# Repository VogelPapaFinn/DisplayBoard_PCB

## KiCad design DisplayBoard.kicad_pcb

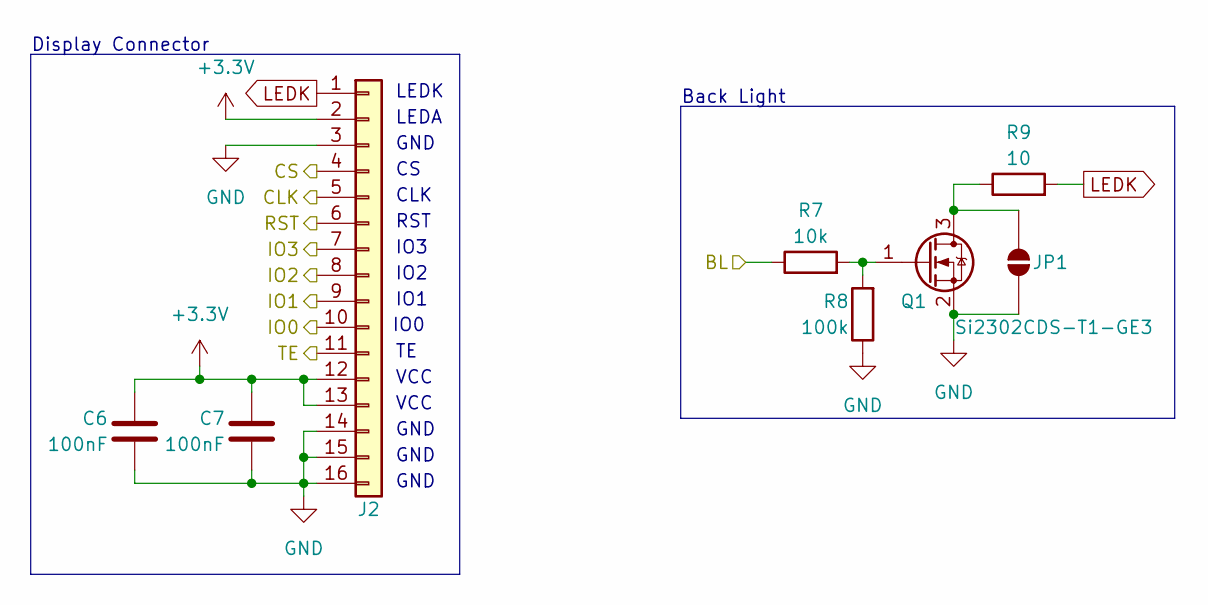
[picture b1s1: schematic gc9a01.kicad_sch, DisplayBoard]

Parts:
C6, C7: 100nF; C_0805_2012Metric
J2: Conn_01x16; ST77916
JP1: SolderJumper_2_Open; SolderJumper-2_P1.3mm_Open_Pad1.0x1.5mm
Q1: Si2302CDS-T1-GE3; SOT-23
R7: 10k; R_0603_1608Metric
R8: 100k; R_0603_1608Metric
R9: 10; R_0603_1608Metric

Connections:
+3.3V: C6.1, C7.1, J2.2, J2.12, J2.13; also elsewhere on the board
/Display/BL: R7.1; also elsewhere on the board
/Display/CLK: J2.5; also elsewhere on the board
/Display/CS: J2.4; also elsewhere on the board
/Display/IO0: J2.10; also elsewhere on the board
/Display/IO1: J2.9; also elsewhere on the board
/Display/IO2: J2.8; also elsewhere on the board
/Display/IO3: J2.7; also elsewhere on the board
/Display/RST: J2.6; also elsewhere on the board
/Display/TE: J2.11; also elsewhere on the board
GND: C6.2, C7.2, J2.3, J2.14, J2.15, J2.16, JP1.2 (B), Q1.2 (S), R8.1; also elsewhere on the board
LEDK: J2.1, R9.2
unnamed: JP1.1 (A), Q1.3 (D), R9.1
unnamed: Q1.1 (G), R7.2, R8.2

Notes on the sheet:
IO1
IO0
GND
VCC
LEDA
Display Connector
Back Light
IO2
CLK
LEDK
RST
IO3

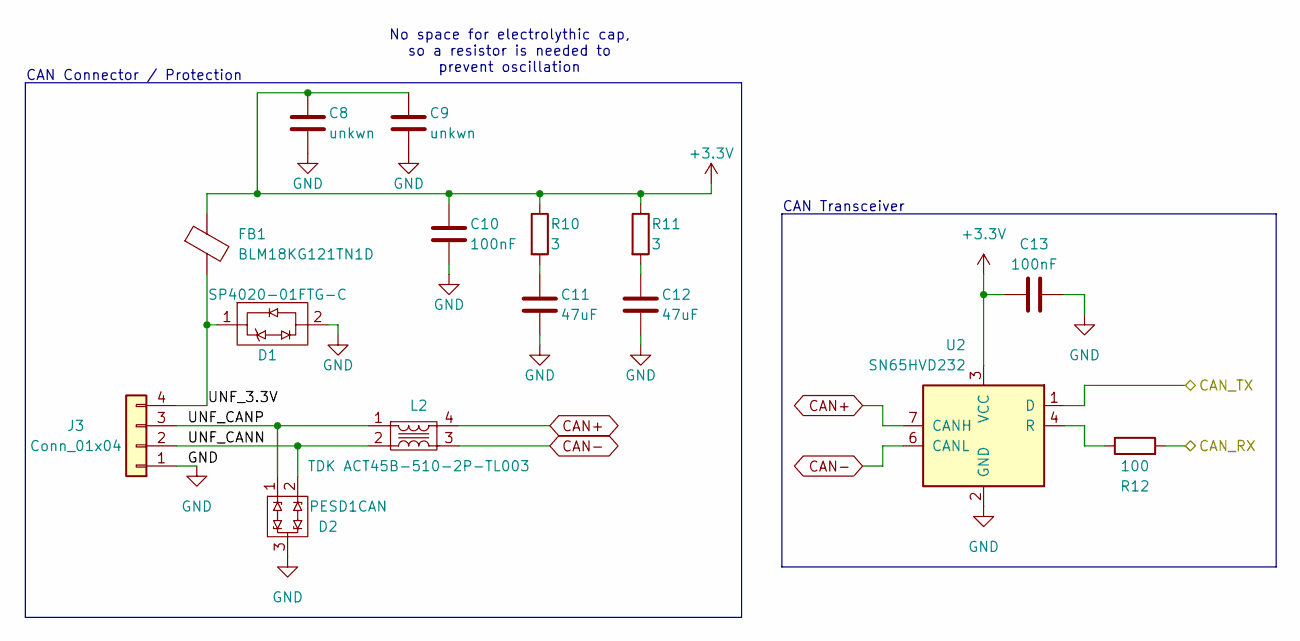
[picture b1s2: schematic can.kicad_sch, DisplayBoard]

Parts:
C8, C9: unkwn; C_0805_2012Metric
C10, C13: 100nF; C_0805_2012Metric
C11, C12: 47uF; C_0805_2012Metric
D1: SP4020-01FTG-C; D_SOD-323
D2: PESD1CAN; SOT-23
FB1: BLM18KG121TN1D; L_0603_1608Metric
J3: Conn_01x04; JST_PH_B4B-PH-SM4-TB_1x04-1MP_P2.00mm_Vertical
L2: TDK ACT45B-510-2P-TL003
R10, R11: 3; R_0603_1608Metric
R12: 100; R_0603_1608Metric
U2: SN65HVD232; SOIC-8_3.9x4.9mm_P1.27mm

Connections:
+3.3V: C8.1, C9.1, C10.1, C13.1, FB1.1, R10.1, R11.1, U2.3 (VCC); also elsewhere on the board
/CAN/CAN_RX: R12.2; also elsewhere on the board
/CAN/CAN_TX: U2.1 (D); also elsewhere on the board
/CAN/UNF_3.3V: D1.1, FB1.2, J3.4
/CAN/UNF_CANN: D2.2, J3.2, L2.2
/CAN/UNF_CANP: D2.1, J3.3, L2.1
CAN+: L2.4, U2.7 (CANH)
CAN-: L2.3, U2.6 (CANL)
GND: C8.2, C9.2, C10.2, C11.2, C12.2, C13.2, D1.2, D2.3, J3.1, U2.2 (GND); also elsewhere on the board
unnamed: C11.1, R10.2
unnamed: C12.1, R11.2
unnamed: R12.1, U2.4 (R)

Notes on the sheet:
No space for electrolythic cap, so a resistor is needed to prevent oscillation
CAN Transceiver
CAN Connector / Protection

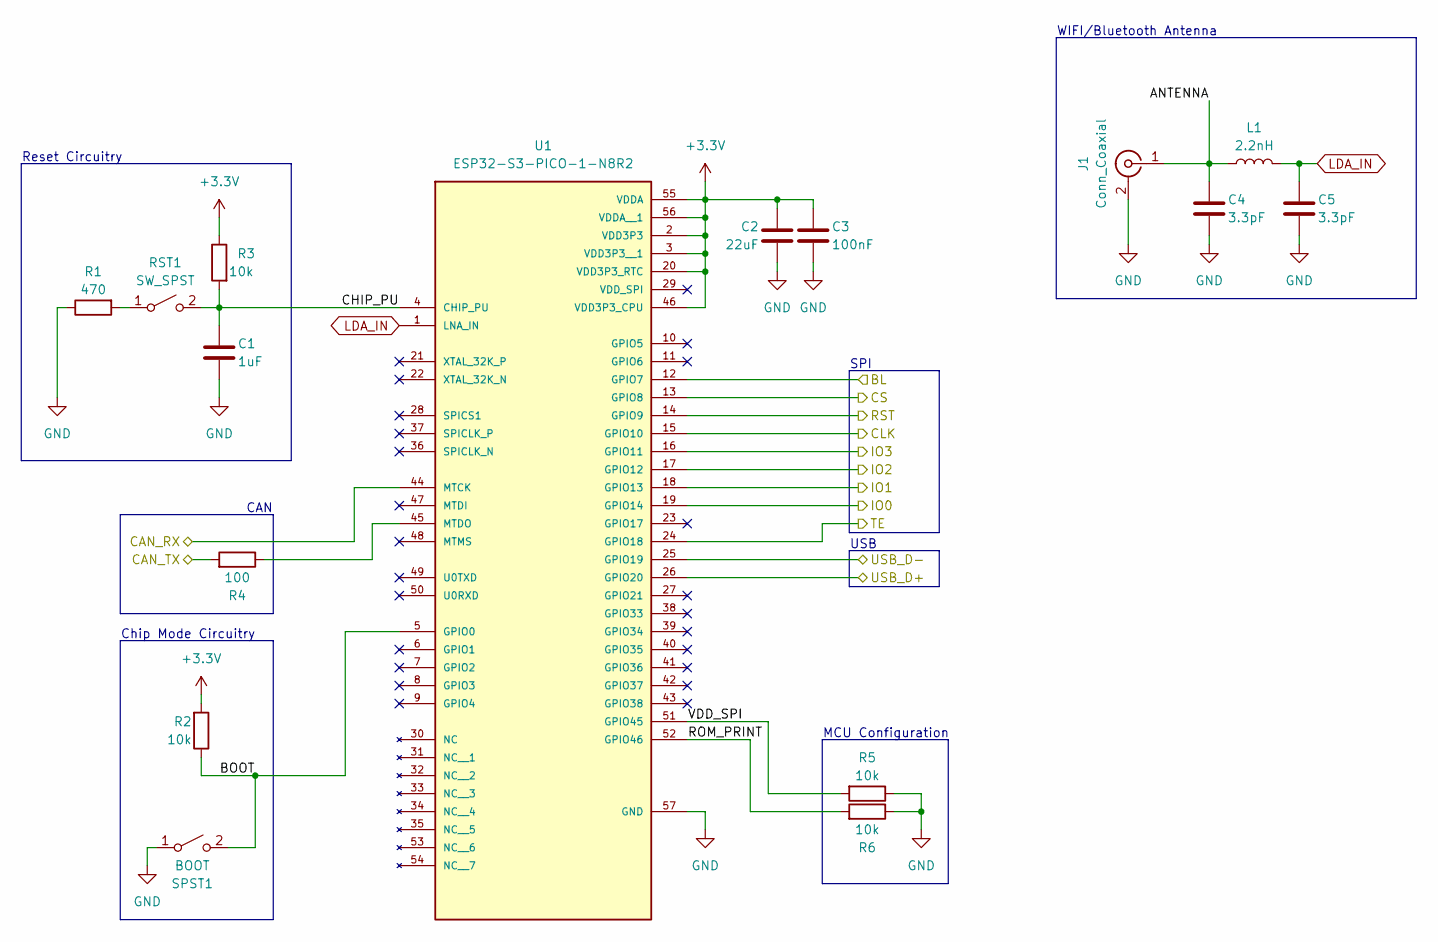
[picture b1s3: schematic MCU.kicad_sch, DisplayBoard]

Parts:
C1: 1uF; C_0805_2012Metric
C2: 22uF; C_0805_2012Metric
C3: 100nF; C_0805_2012Metric
C4, C5: 3.3pF; C_0603_1608Metric
J1: Conn_Coaxial; CONMHF1-SMD-G-T_U.FL
L1: 2.2nH; L_0603_1608Metric
R1: 470; R_0603_1608Metric
R2, R3, R5, R6: 10k; R_0603_1608Metric
R4: 100; R_0603_1608Metric
RST1: SW_SPST; XUNPU_Button
SPST1: BOOT; XUNPU_Button
U1: ESP32-S3-PICO-1-N8R2; ESP32-S3-PICO-1; PARTREV 1.0

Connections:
+3.3V: C2.1, C3.1, R2.2, R3.1, U1.2 (VDD3P3), U1.3 (VDD3P3__1), U1.20 (VDD3P3_RTC), U1.46 (VDD3P3_CPU), U1.55 (VDDA), U1.56 (VDDA__1); also elsewhere on the board
/CAN/CAN_RX: U1.44 (MTCK); also elsewhere on the board
/CAN/CAN_TX: R4.2; also elsewhere on the board
/Display/BL: U1.12 (GPIO7); also elsewhere on the board
/Display/CLK: U1.15 (GPIO10); also elsewhere on the board
/Display/CS: U1.13 (GPIO8); also elsewhere on the board
/Display/IO0: U1.19 (GPIO14); also elsewhere on the board
/Display/IO1: U1.18 (GPIO13); also elsewhere on the board
/Display/IO2: U1.17 (GPIO12); also elsewhere on the board
/Display/IO3: U1.16 (GPIO11); also elsewhere on the board
/Display/RST: U1.14 (GPIO9); also elsewhere on the board
/Display/TE: U1.24 (GPIO18); also elsewhere on the board
/MCU/ANTENNA: C4.1, J1.1 (In), L1.1
/MCU/BOOT: R2.1, SPST1.2 (B), U1.5 (GPIO0)
/MCU/CHIP_PU: C1.1, R3.2, RST1.2 (B), U1.4 (CHIP_PU)
/MCU/ROM_PRINT: R6.2, U1.52 (GPIO46)
/MCU/USB_D+: U1.26 (GPIO20); also elsewhere on the board
/MCU/USB_D-: U1.25 (GPIO19); also elsewhere on the board
/MCU/VDD_SPI: R5.2, U1.51 (GPIO45)
GND: C1.2, C2.2, C3.2, C4.2, C5.2, J1.2 (Ext), R1.1, R5.1, R6.1, SPST1.1 (A), U1.57 (GND); also elsewhere on the board
LDA_IN: C5.1, L1.2, U1.1 (LNA_IN)
unnamed: R1.2, RST1.1 (A)
unnamed: R4.1, U1.45 (MTDO)

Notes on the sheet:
Chip Mode Circuitry
USB
Reset Circuitry
WIFI/Bluetooth Antenna
MCU Configuration
SPI
CAN

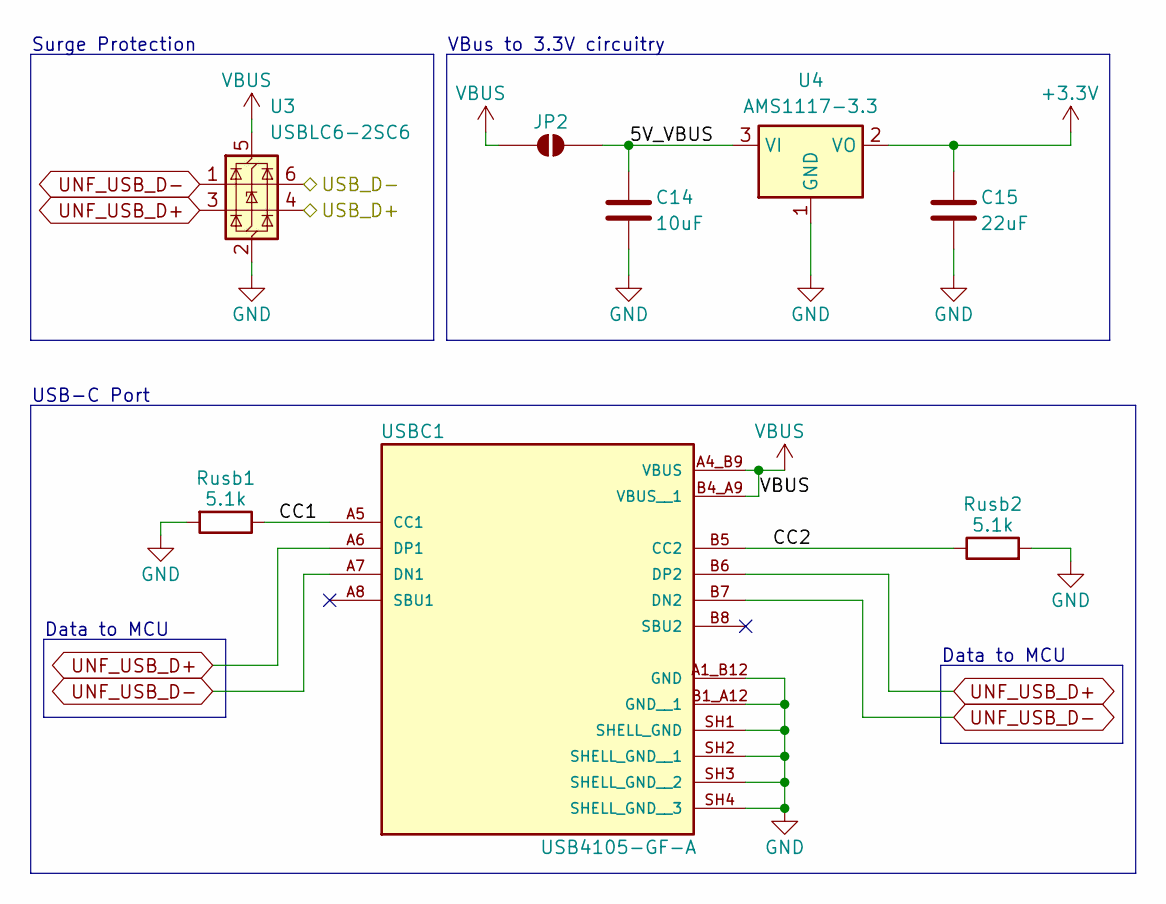
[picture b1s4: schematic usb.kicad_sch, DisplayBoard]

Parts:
C14: 10uF; C_0805_2012Metric
C15: 22uF; C_0805_2012Metric
JP2: SolderJumper_2_Open; SolderJumper-2_P1.3mm_Open_RoundedPad1.0x1.5mm
Rusb1, Rusb2: 5.1k; R_0603_1608Metric
U3: USBLC6-2SC6; SOT-23-6
U4: AMS1117-3.3; SOT-223-3_TabPin2
USBC1: USB4105-GF-A; USB-C_24P-2.0; PARTREV B4

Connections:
+3.3V: C15.1, U4.2 (VO); also elsewhere on the board
/MCU/USB_D+: U3.4 (I/O2); also elsewhere on the board
/MCU/USB_D-: U3.6 (I/O1); also elsewhere on the board
/USB/5V_VBUS: C14.1, JP2.2 (B), U4.3 (VI)
/USB/CC1: Rusb1.1, USBC1.A5 (CC1)
/USB/CC2: Rusb2.1, USBC1.B5 (CC2)
GND: C14.2, C15.2, Rusb1.2, Rusb2.2, U3.2 (GND), U4.1 (GND), USBC1.A1_B12 (GND), USBC1.B1_A12 (GND__1), USBC1.SH1 (SHELL_GND), USBC1.SH2 (SHELL_GND__1), USBC1.SH3 (SHELL_GND__2), USBC1.SH4 (SHELL_GND__3); also elsewhere on the board
UNF_USB_D+: U3.3 (I/O2), USBC1.A6 (DP1), USBC1.B6 (DP2)
UNF_USB_D-: U3.1 (I/O1), USBC1.A7 (DN1), USBC1.B7 (DN2)
VBUS: JP2.1 (A), U3.5 (VBUS), USBC1.A4_B9 (VBUS), USBC1.B4_A9 (VBUS__1)

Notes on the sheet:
Data to MCU
Surge Protection
VBus to 3.3V circuitry
USB-C Port

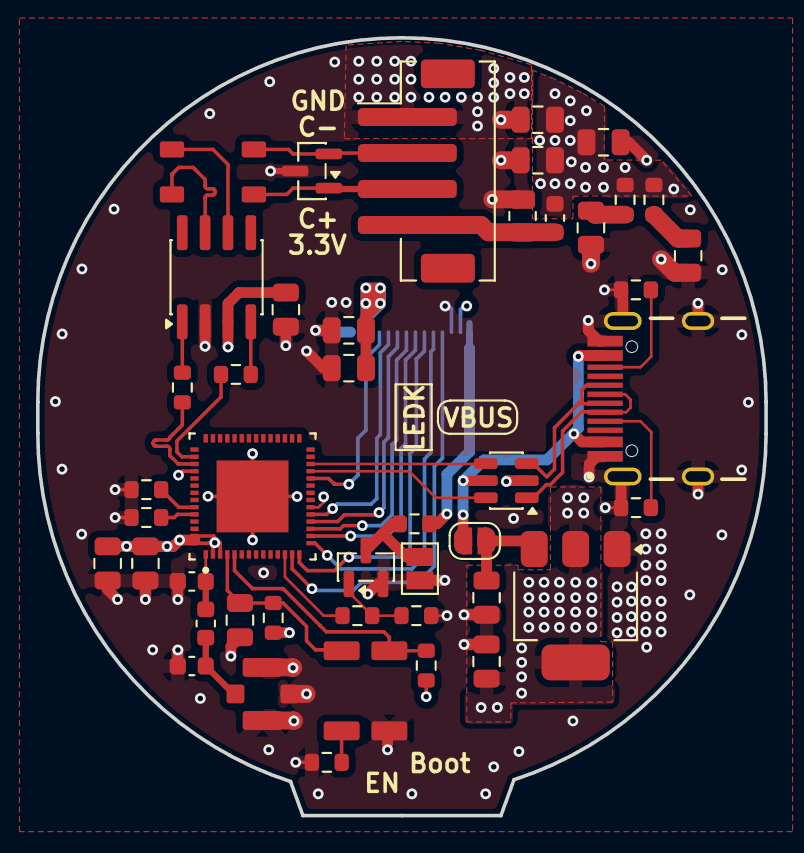
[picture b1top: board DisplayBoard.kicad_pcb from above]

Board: 4 copper layers, 40.5 x 43.2 mm, 47 parts (1 on the bottom side), 40 nets.

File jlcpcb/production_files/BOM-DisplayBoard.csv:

Comment,Designator,Footprint,LCSC,Quantity
10k,R7,R_0603_1608Metric,,1
3.3pF,C5,C_0603_1608Metric,,1
Si2302CDS-T1-GE3,Q1,SOT-23,,1
10k,R3,R_0603_1608Metric,,1
47uF,C11,C_0805_2012Metric,,1
100nF,C13,C_0805_2012Metric,,1
unkwn,C8,C_0805_2012Metric,,1
2.2nH,L1,L_0603_1608Metric,,1
470,R1,R_0603_1608Metric,,1
unkwn,C9,C_0805_2012Metric,,1
SW_SPST,RST1,XUNPU_Button,,1
1uF,C1,C_0805_2012Metric,,1
TDK ACT45B-510-2P-TL003,L2,TDK ACT45B-510-2P-TL003,,1
47uF,C12,C_0805_2012Metric,,1
USB4105-GF-A,USBC1,USB-C_24P-2.0,,1
10,R9,R_0603_1608Metric,,1
100,R12,R_0603_1608Metric,,1
USBLC6-2SC6,U3,SOT-23-6,,1
BOOT,SPST1,XUNPU_Button,,1
SP4020-01FTG-C,D1,R_0805_2012Metric,,1
22uF,C15,C_0805_2012Metric,,1
100,R4,R_0603_1608Metric,,1
10uF,C14,C_0805_2012Metric,,1
3,R10,R_0603_1608Metric,,1
PESD1CAN,D2,SOT-23,,1
AMS1117-3.3,U4,SOT-223-3_TabPin2,,1
100k,R8,R_0603_1608Metric,,1
10k,R5,R_0603_1608Metric,,1
10k,R2,R_0603_1608Metric,,1
5.1k,Rusb1,R_0603_1608Metric,,1
100nF,C3,C_0805_2012Metric,,1
Conn_Coaxial,J1,CONMHF1-SMD-G-T_U.FL,,1
BLM18KG121TN1D,FB1,L_0603_1608Metric,,1
100nF,C6,C_0805_2012Metric,,1
22uF,C2,C_0805_2012Metric,,1
3.3pF,C4,C_0603_1608Metric,,1
10k,R6,R_0603_1608Metric,,1
ESP32-S3-PICO-1-N8R2,U1,ESP32-S3-PICO-1,,1
SN65HVD232,U2,SOIC-8_3.9x4.9mm_P1.27mm,,1
Conn_01x04,J3,JST_PH_B4B-PH-SM4-TB_1x04-1MP_P2.00mm_Vertical,,1
5.1k,Rusb2,R_0603_1608Metric,,1
100nF,C10,C_0805_2012Metric,,1
3,R11,R_0603_1608Metric,,1
100nF,C7,C_0805_2012Metric,,1
Conn_01x16,J2,AFC01-S16FCC-00,,1

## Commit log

2026-01-31 Reworked DisplayBoard circuitry and layout; v1.1
2026-01-31 Fixed missing 3D model
2026-02-01 Fixed wrong board outlines
2026-04-10 Finished v1.1
2026-05-02 Silkscreen touchups & gerbers
